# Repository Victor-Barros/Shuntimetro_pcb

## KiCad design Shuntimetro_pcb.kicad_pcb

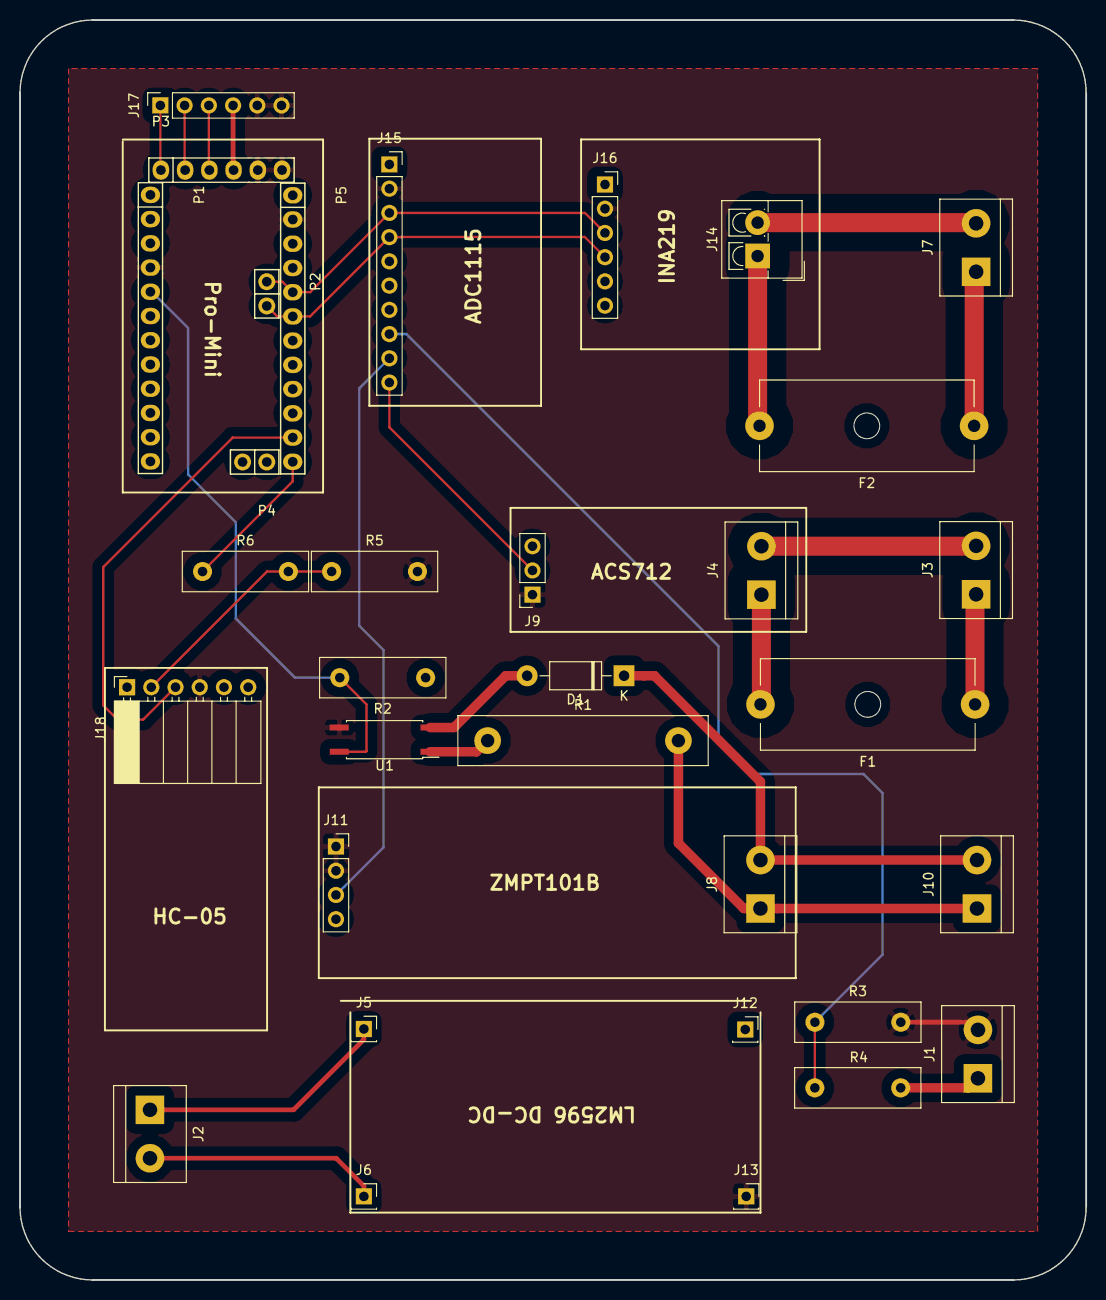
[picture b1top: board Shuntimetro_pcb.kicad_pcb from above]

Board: 2 copper layers, 111.8 x 132.1 mm, 33 parts (0 on the bottom side), 27 nets.

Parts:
D1: 1N4007; D_DO-41_SOD81_P10.16mm_Horizontal
F1: HC Fuse; Fuseholder_Cylinder-5x20mm_Schurter_0031_8201_Horizontal_Op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
F2: LC Fuse; Fuseholder_Cylinder-5x20mm_Schurter_0031_8201_Horizontal_Op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
J1: Terminal de Baixa Tensão; TerminalBlock_bornier-2_P5.08mm
J2: Terminal de Bateria; TerminalBlock_bornier-2_P5.08mm
J3: Terminal de Corrente Alta; TerminalBlock_bornier-2_P5.08mm
J4: Entrada de Corrente Al; TerminalBlock_bornier-2_P5.08mm
J5: Entrada + (Buck); PinSocket_1x01_P2.54mm_Vertical
J6: Entrada - (Buck); PinSocket_1x01_P2.54mm_Vertical
J7: Terminal de Corrente Baixa; TerminalBlock_bornier-2_P5.08mm
J8: Entrada de Tensão CA; TerminalBlock_bornier-2_P5.08mm
J9: Saída Analógica - Energia (ACS712); PinSocket_1x03_P2.54mm_Vertical
J10: Terminal de Alta Tensão (CA); TerminalBlock_bornier-2_P5.08mm
J11: Saida Analógica - Energia (ZMP1101B); PinSocket_1x04_P2.54mm_Vertical
J12: Saída + (Buck); PinSocket_1x01_P2.54mm_Vertical
J13: Saída - (Buck); PinSocket_1x01_P2.54mm_Vertical
J14: Entrada de Corrente Bx; TerminalBlock_4Ucon_1x02_P3.50mm_Vertical
J15: I2C - Energia - Entradas (ADC1115); PinSocket_1x10_P2.54mm_Vertical
J16: I2C - Energia (INA219); PinSocket_1x06_P2.54mm_Vertical
J17: Header de Programação; PinSocket_1x06_P2.54mm_Vertical
J18: Energia - Serial (HC-05); PinSocket_1x06_P2.54mm_Horizontal
P1: Digital; Socket_Strip_Arduino_1x12
P2: I2C; Socket_Strip_Arduino_1x02
P3: COM; Socket_Strip_Arduino_1x06
P4: ADC; Socket_Strip_Arduino_1x02
P5: Analog; Socket_Strip_Arduino_1x12
R1: 47k; R_Box_L26.0mm_W5.0mm_P20.00mm
R2: 10k; R_Box_L13.0mm_W4.0mm_P9.00mm
R3: 100k; R_Box_L13.0mm_W4.0mm_P9.00mm
R4: 1M; R_Box_L13.0mm_W4.0mm_P9.00mm
R5: 2k; R_Box_L13.0mm_W4.0mm_P9.00mm
R6: 1k; R_Box_L13.0mm_W4.0mm_P9.00mm
U1: EL814; SO-4_7.6x3.6mm_P2.54mm

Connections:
/0(Rx): J17.3, P3.3
/1(Tx): J17.2, P3.2
/2(INT0): P1.5, R2.2, U1.4
/10(**/SS): P5.12, R6.1
/11(**/MOSI): J18.3, P5.11
/A1: J15.8, R3.1, R4.2
/A2: J11.3, J15.9
/A3: J9.2, J15.10
/DTR: J17.1, P3.1
/RX: J18.2, R5.1, R6.2
/SCL: J15.3, J16.3, P2.1, P5.5
/SDA: J15.4, J16.4, P2.2, P5.6
/V+: F2.2, J14.1
/V-: J7.2, J14.2
GND: J1.2, J9.1, J11.1, J11.2, J13.1, J15.2, J16.2, J17.5, J17.6, J18.4, P1.4, P3.5, P3.6, P5.2, R3.2, R5.2, U1.3
unnamed: D1.1, J8.2, J10.2
unnamed: D1.2, U1.2
unnamed: F1.1, J3.1
unnamed: F1.2, J4.1
unnamed: F2.1, J7.1
unnamed: J1.1, R4.1
unnamed: J2.1, J5.1
unnamed: J2.2, J6.1
unnamed: J3.2, J4.2
unnamed: J8.1, J10.1, R1.2
unnamed: R1.1, U1.1
VCC: J9.3, J11.4, J12.1, J15.1, J16.1, J17.4, J18.5, P3.4, P5.4, R2.1

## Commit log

2018-10-12 Fusivel modificado
